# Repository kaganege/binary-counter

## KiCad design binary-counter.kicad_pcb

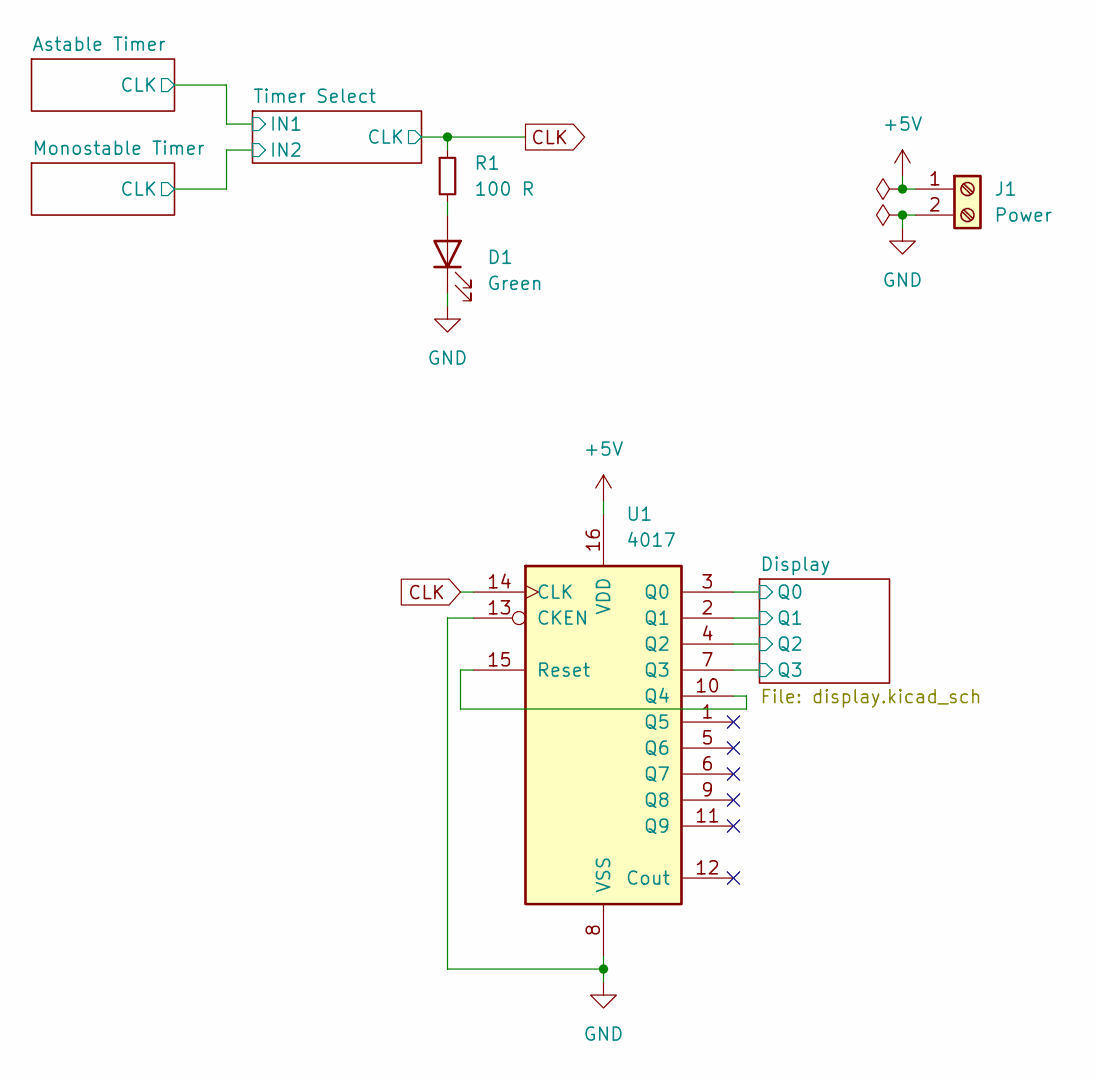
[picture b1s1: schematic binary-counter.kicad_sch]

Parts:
D1: Green; LED_D5.0mm
J1: Power; TerminalBlock_4Ucon_1x02_P3.50mm_Horizontal
R1: 100 R; R_Axial_DIN0207_L6.3mm_D2.5mm_P10.16mm_Horizontal
U1: 4017; DIP-16_W7.62mm_Socket

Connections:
+5V: J1.1, U1.16 (VDD); also elsewhere on the board
/Display/Q0: U1.3 (Q0); also elsewhere on the board
/Display/Q1: U1.2 (Q1); also elsewhere on the board
/Display/Q2: U1.4 (Q2); also elsewhere on the board
/Display/Q3: U1.7 (Q3); also elsewhere on the board
CLK: R1.1, U1.14 (CLK); also elsewhere on the board
GND: D1.1 (K), J1.2, U1.8 (VSS), U1.13 (CKEN); also elsewhere on the board
unnamed: D1.2 (A), R1.2
unnamed: U1.10 (Q4), U1.15 (Reset)

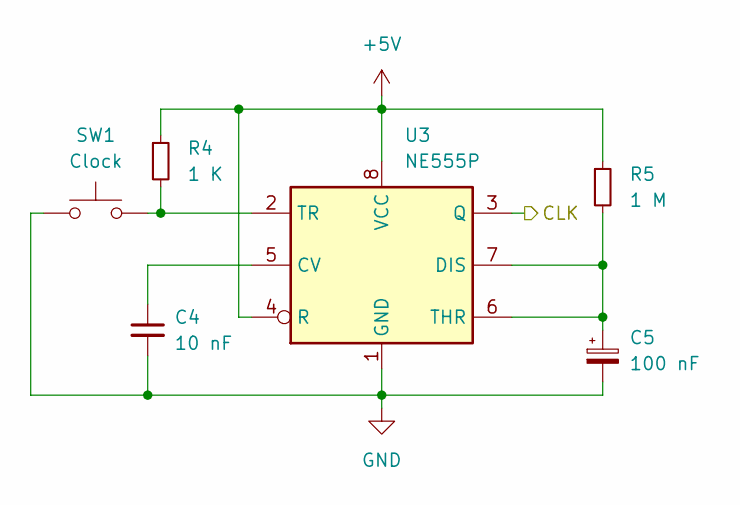
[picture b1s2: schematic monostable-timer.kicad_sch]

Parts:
C4: 10 nF; C_Disc_D7.5mm_W5.0mm_P5.00mm
C5: 100 nF; CP_Radial_D5.0mm_P2.50mm
R4: 1 K; R_Axial_DIN0207_L6.3mm_D2.5mm_P10.16mm_Horizontal
R5: 1 M; R_Axial_DIN0207_L6.3mm_D2.5mm_P10.16mm_Horizontal
SW1: Clock; SW_PUSH_6mm
U3: NE555P; DIP-8_W7.62mm_Socket

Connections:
+5V: R4.1, R5.1, U3.4 (R), U3.8 (VCC); also elsewhere on the board
/Monostable Timer/CLK: U3.3 (Q); also elsewhere on the board
GND: C4.2, C5.2, SW1.1, U3.1 (GND); also elsewhere on the board
unnamed: C4.1, U3.5 (CV)
unnamed: C5.1, R5.2, U3.6 (THR), U3.7 (DIS)
unnamed: R4.2, SW1.2, U3.2 (TR)

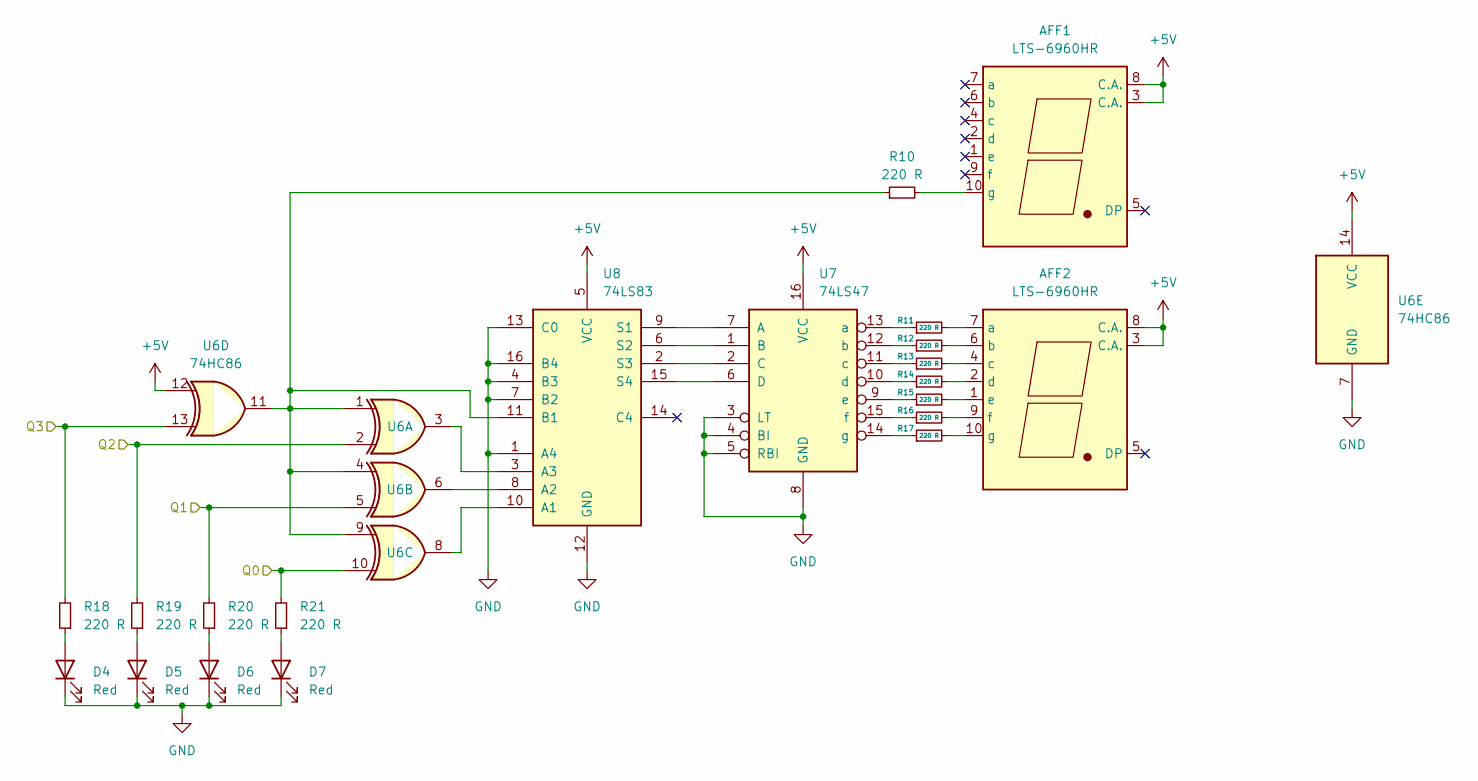
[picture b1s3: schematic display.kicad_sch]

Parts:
AFF1, AFF2: LTS-6960HR; 7SegmentLED_LTS6760_LTS6780
D4, D5, D6, D7: Red; LED_D5.0mm
R10, R11, R12, R13, R14, R15, R16, R17, R18, R19, R20, R21: 220 R; R_Axial_DIN0207_L6.3mm_D2.5mm_P10.16mm_Horizontal
U6: 74HC86; DIP-14_W7.62mm_Socket
U7: 74LS47; DIP-16_W7.62mm_Socket
U8: 74LS83; DIP-16_W7.62mm_Socket

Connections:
+5V: AFF1.3 (C.A.), AFF1.8 (C.A.), AFF2.3 (C.A.), AFF2.8 (C.A.), U6.12, U6.14 (VCC), U7.16 (VCC), U8.5 (VCC); also elsewhere on the board
/Display/Q0: R21.2, U6.10; also elsewhere on the board
/Display/Q1: R20.2, U6.5; also elsewhere on the board
/Display/Q2: R19.2, U6.2; also elsewhere on the board
/Display/Q3: R18.2, U6.13; also elsewhere on the board
GND: D4.1 (K), D5.1 (K), D6.1 (K), D7.1 (K), U6.7 (GND), U7.3 (LT), U7.4 (BI), U7.5 (RBI), U7.8 (GND), U8.1 (A4), U8.4 (B3), U8.7 (B2), U8.12 (GND), U8.13 (C0), U8.16 (B4); also elsewhere on the board
unnamed: AFF1.10 (g), R10.2
unnamed: AFF2.7 (a), R11.2
unnamed: AFF2.6 (b), R12.2
unnamed: AFF2.4 (c), R13.2
unnamed: AFF2.2 (d), R14.2
unnamed: AFF2.1 (e), R15.2
unnamed: AFF2.9 (f), R16.2
unnamed: AFF2.10 (g), R17.2
unnamed: D4.2 (A), R18.1
unnamed: D5.2 (A), R19.1
unnamed: D6.2 (A), R20.1
unnamed: D7.2 (A), R21.1
unnamed: U7.7 (A), U8.9 (S1)
unnamed: U7.1 (B), U8.6 (S2)
unnamed: U7.2 (C), U8.2 (S3)
unnamed: U7.6 (D), U8.15 (S4)
unnamed: R11.1, U7.13 (a)
unnamed: R12.1, U7.12 (b)
unnamed: R13.1, U7.11 (c)
unnamed: R14.1, U7.10 (d)
unnamed: R15.1, U7.9 (e)
unnamed: R16.1, U7.15 (f)
unnamed: R17.1, U7.14 (g)
unnamed: U6.8, U8.10 (A1)
unnamed: U6.6, U8.8 (A2)
unnamed: U6.3, U8.3 (A3)
unnamed: R10.1, U6.1, U6.4, U6.9, U6.11, U8.11 (B1)

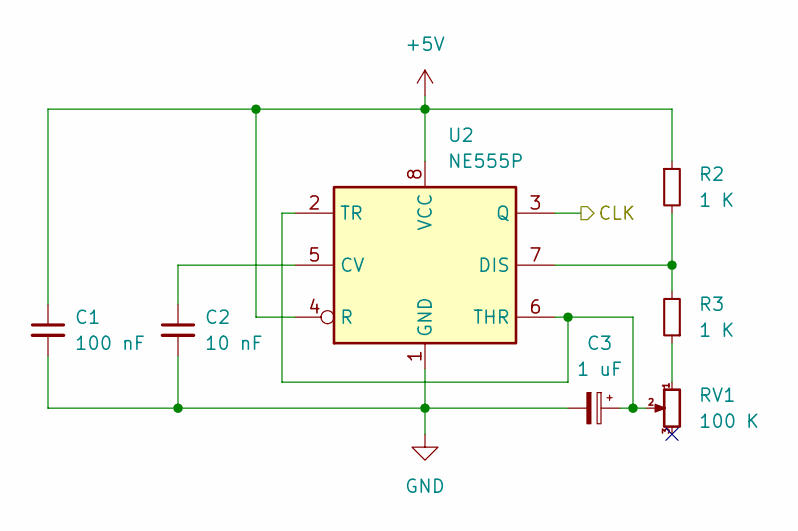
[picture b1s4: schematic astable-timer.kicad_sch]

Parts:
C1: 100 nF; C_Disc_D7.5mm_W5.0mm_P5.00mm
C2: 10 nF; C_Disc_D7.5mm_W5.0mm_P5.00mm
C3: 1 uF; CP_Radial_D5.0mm_P2.50mm
R2, R3: 1 K; R_Axial_DIN0207_L6.3mm_D2.5mm_P10.16mm_Horizontal
RV1: 100 K; Potentiometer_Bourns_3296W_Vertical
U2: NE555P; DIP-8_W7.62mm_Socket

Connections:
+5V: C1.1, R2.1, U2.4 (R), U2.8 (VCC); also elsewhere on the board
/Astable Timer/CLK: U2.3 (Q); also elsewhere on the board
GND: C1.2, C2.2, C3.2, U2.1 (GND); also elsewhere on the board
unnamed: R3.1, RV1.1
unnamed: C2.1, U2.5 (CV)
unnamed: R2.2, R3.2, U2.7 (DIS)
unnamed: C3.1, RV1.2, U2.2 (TR), U2.6 (THR)

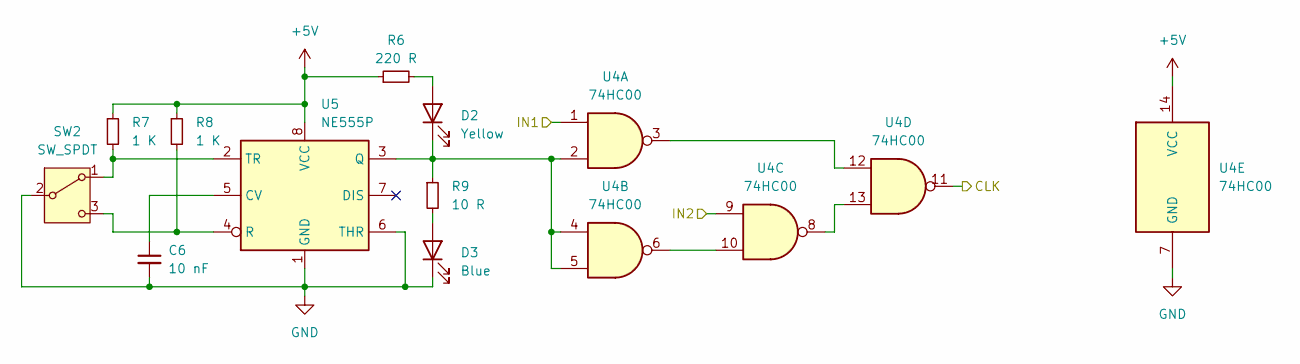
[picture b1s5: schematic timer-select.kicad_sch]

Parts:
C6: 10 nF; C_Disc_D7.5mm_W5.0mm_P5.00mm
D2: Yellow; LED_D5.0mm
D3: Blue; LED_D5.0mm
R6: 220 R; R_Axial_DIN0207_L6.3mm_D2.5mm_P10.16mm_Horizontal
R7, R8: 1 K; R_Axial_DIN0207_L6.3mm_D2.5mm_P10.16mm_Horizontal
R9: 10 R; R_Axial_DIN0207_L6.3mm_D2.5mm_P10.16mm_Horizontal
SW2: SW_SPDT; IC-205
U4: 74HC00; DIP-14_W7.62mm_Socket
U5: NE555P; DIP-8_W7.62mm_Socket

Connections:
+5V: R6.1, R7.1, R8.1, U4.14 (VCC), U5.8 (VCC); also elsewhere on the board
/Astable Timer/CLK: U4.1; also elsewhere on the board
/Monostable Timer/CLK: U4.9; also elsewhere on the board
CLK: U4.11; also elsewhere on the board
GND: C6.2, D3.1 (K), SW2.2 (B), U4.7 (GND), U5.1 (GND), U5.6 (THR); also elsewhere on the board
unnamed: D2.2 (A), R6.2
unnamed: D2.1 (K), R9.1, U4.2, U4.4, U4.5, U5.3 (Q)
unnamed: D3.2 (A), R9.2
unnamed: R7.2, SW2.1 (A), U5.2 (TR)
unnamed: R8.2, SW2.3 (C), U5.4 (R)
unnamed: U4.6, U4.10
unnamed: U4.3, U4.12
unnamed: U4.8, U4.13
unnamed: C6.1, U5.5 (CV)

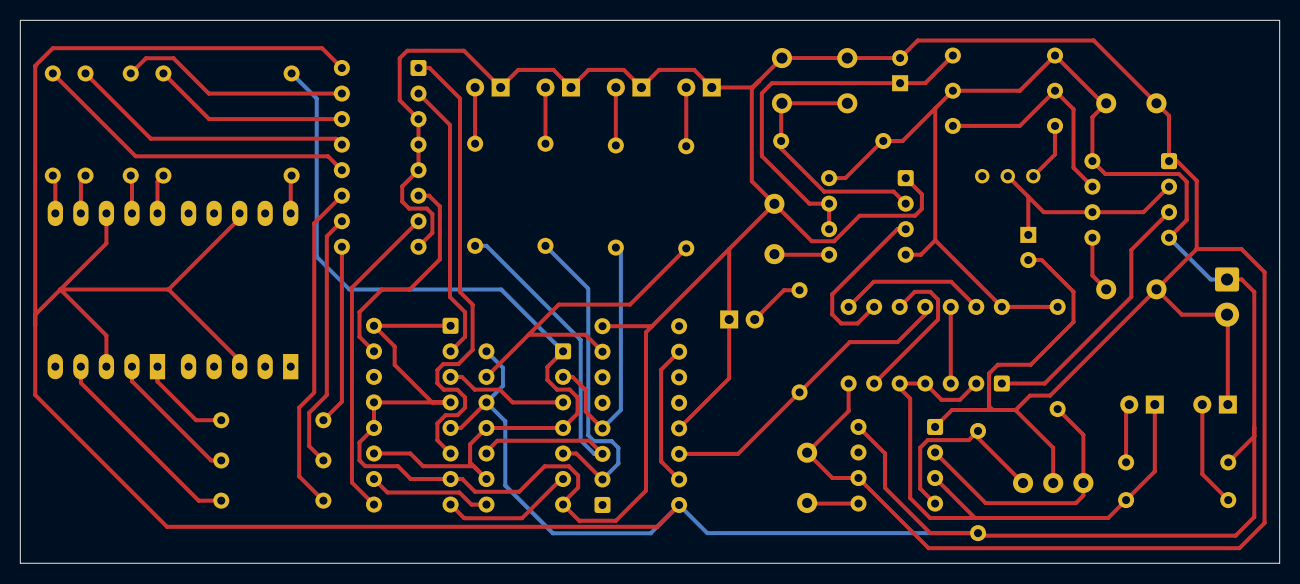
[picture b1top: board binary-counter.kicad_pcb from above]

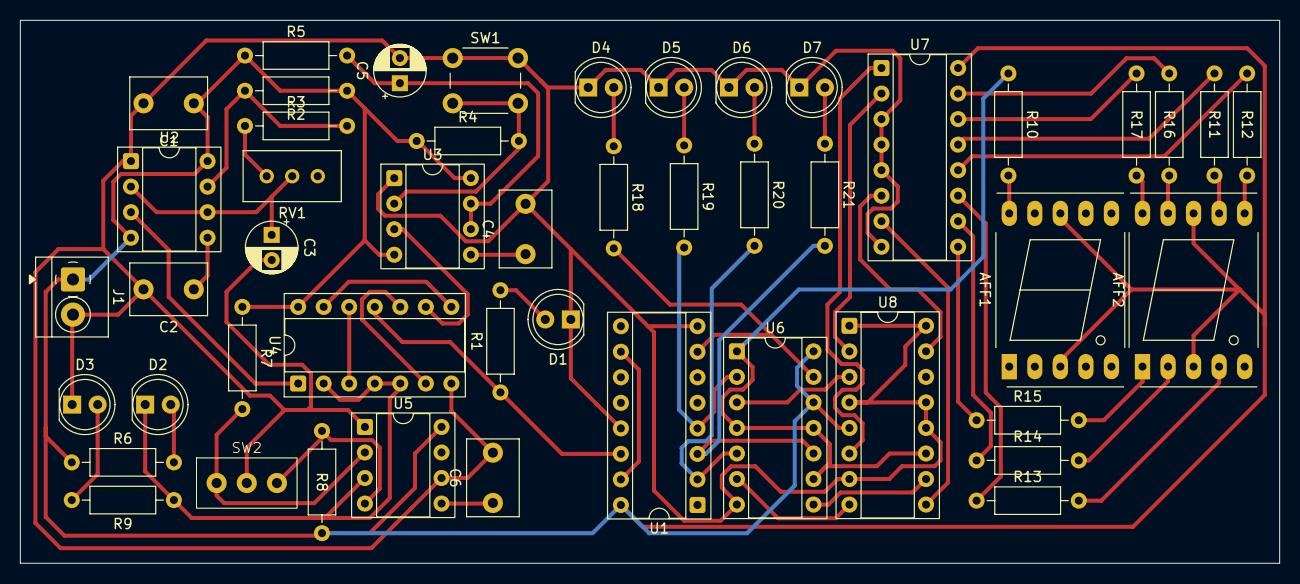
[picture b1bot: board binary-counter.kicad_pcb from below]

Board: 2 copper layers, 125.2 x 54.0 mm, 48 parts (48 on the bottom side), 54 nets.

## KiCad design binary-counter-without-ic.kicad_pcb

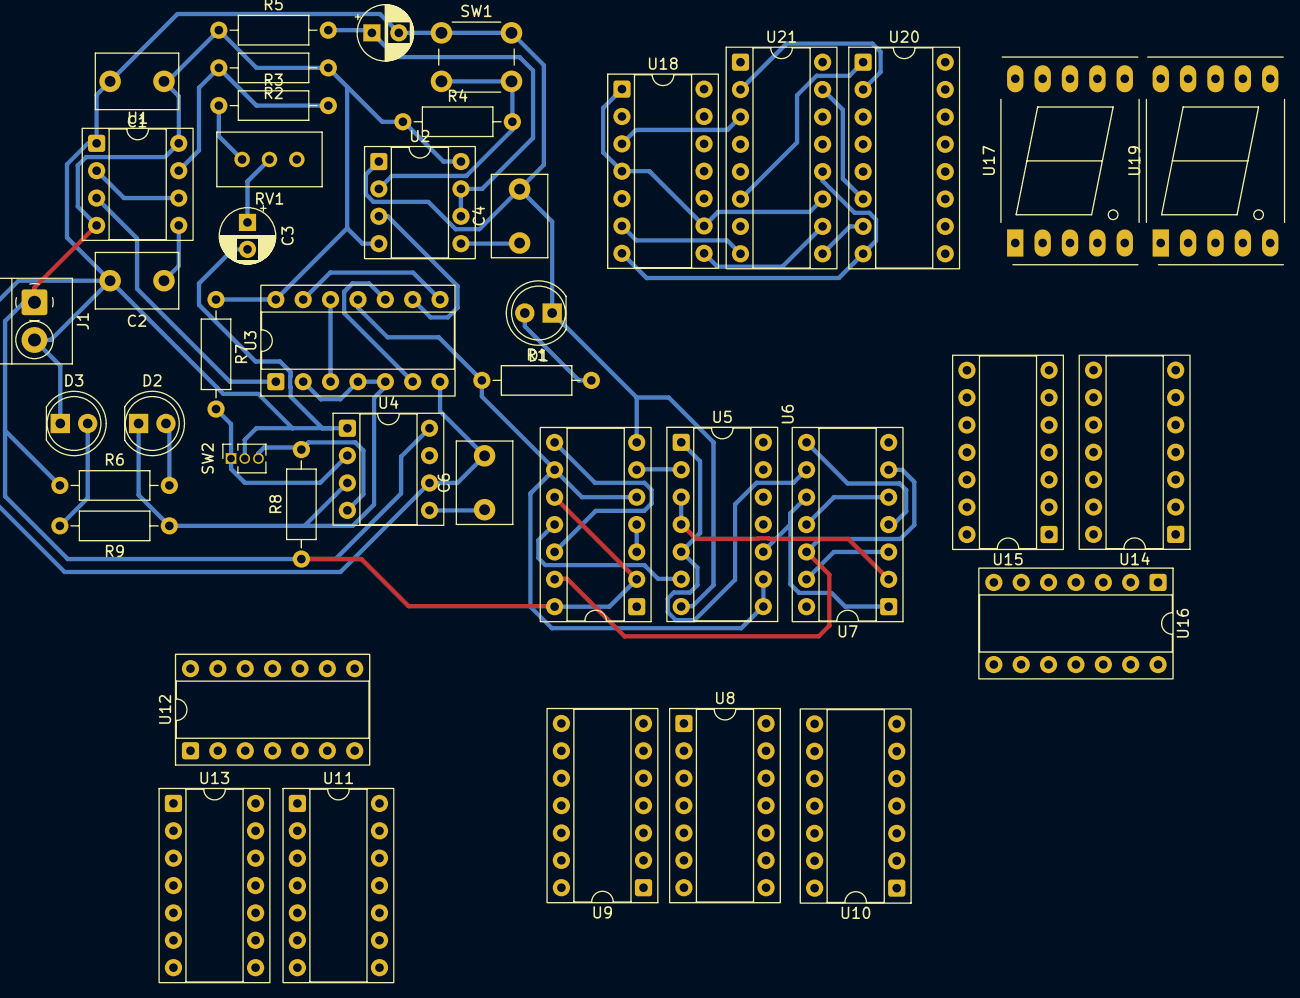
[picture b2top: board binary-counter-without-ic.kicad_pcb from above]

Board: 2 copper layers, 43 parts (0 on the bottom side), 81 nets.

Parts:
C1: 100 nF; C_Disc_D7.5mm_W5.0mm_P5.00mm
C2, C4, C6: 10 nF; C_Disc_D7.5mm_W5.0mm_P5.00mm
C3: 1 uF; CP_Radial_D5.0mm_P2.50mm
C5: 100 nF; CP_Radial_D5.0mm_P2.50mm
D1: Green; LED_D5.0mm
D2: Yellow; LED_D5.0mm
D3: Blue; LED_D5.0mm
J1: Power; TerminalBlock_4Ucon_1x02_P3.50mm_Horizontal
R1: 100 R; R_Axial_DIN0207_L6.3mm_D2.5mm_P10.16mm_Horizontal
R2, R3, R4, R7, R8: 1 K; R_Axial_DIN0207_L6.3mm_D2.5mm_P10.16mm_Horizontal
R5: 1 M; R_Axial_DIN0207_L6.3mm_D2.5mm_P10.16mm_Horizontal
R6: 220 R; R_Axial_DIN0207_L6.3mm_D2.5mm_P10.16mm_Horizontal
R9: 10 R; R_Axial_DIN0207_L6.3mm_D2.5mm_P10.16mm_Horizontal
RV1: 100 K; Potentiometer_Bourns_3296W_Vertical
SW1: Clock; SW_PUSH_6mm
SW2: SW_SPDT; PinSocket_1x03_P1.27mm_Vertical
U1, U2, U4: NE555P; DIP-8_W7.62mm_Socket
U3, U7, U10, U13, U16: 74HC00; DIP-14_W7.62mm_Socket
U5, U8, U11, U14: 74HC02; DIP-14_W7.62mm_Socket
U6, U9, U12, U15: 74HC08; DIP-14_W7.62mm_Socket
U17, U19: SM410561K; 7SegmentLED_LTS6760_LTS6780
U18: 74HC86; DIP-14_W7.62mm_Socket
U20: 74LS248; DIP-16_W7.62mm_Socket
U21: 74LS83; DIP-16_W7.62mm_Socket

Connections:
+5V: C1.1, J1.1, R2.1, R4.1, R5.1, R6.1, R7.1, R8.1, U1.4 (R), U1.8 (VCC), U2.4 (R), U2.8 (VCC), U3.14 (VCC), U4.8 (VCC), U5.14 (VCC), U6.2, U6.10, U6.14 (VCC), U7.14 (VCC), U8.14 (VCC), U9.2, U9.10, U9.14 (VCC), U10.14 (VCC), U11.14 (VCC), U12.2, U12.10, U12.14 (VCC), U13.14 (VCC), U14.14 (VCC), U15.2, U15.10, U15.14 (VCC), U16.14 (VCC), U18.14 (VCC), U20.16 (VCC), U21.5 (VCC)
/Astable Timer/CLK: U1.3 (Q), U3.1
/Master-Slave J-K Flip Flop1/3 Input AND Gate/AOUT: U8.2, U9.6
/Master-Slave J-K Flip Flop1/3 Input AND Gate/BOUT: U8.6, U9.11
/Master-Slave J-K Flip Flop1/S-R Latch/EN: U8.10, U10.1, U10.10
/Master-Slave J-K Flip Flop1/S-R Latch/R: U8.3, U8.4, U10.2
/Master-Slave J-K Flip Flop1/S-R Latch/S: U8.1, U8.5, U10.9
/Master-Slave J-K Flip Flop1/~Q: U9.1, U10.5, U10.11
/Master-Slave J-K Flip Flop2/3 Input AND Gate/AOUT: U11.2, U12.6
/Master-Slave J-K Flip Flop2/3 Input AND Gate/BOUT: U11.6, U12.11
/Master-Slave J-K Flip Flop2/S-R Latch/EN: U11.10, U13.1, U13.10
/Master-Slave J-K Flip Flop2/S-R Latch/R: U11.3, U11.4, U13.2
/Master-Slave J-K Flip Flop2/S-R Latch/S: U11.1, U11.5, U13.9
/Master-Slave J-K Flip Flop2/~Q: U12.1, U13.5, U13.11
/Master-Slave J-K Flip Flop3/3 Input AND Gate/AOUT: U14.2, U15.6
/Master-Slave J-K Flip Flop3/3 Input AND Gate/BOUT: U14.6, U15.11
/Master-Slave J-K Flip Flop3/Q: U15.13, U16.6, U16.12
/Master-Slave J-K Flip Flop3/S-R Latch/EN: U14.10, U16.1, U16.10
/Master-Slave J-K Flip Flop3/S-R Latch/R: U14.3, U14.4, U16.2
/Master-Slave J-K Flip Flop3/S-R Latch/S: U14.1, U14.5, U16.9
/Master-Slave J-K Flip Flop/3 Input AND Gate/AOUT: U5.2, U6.6
/Master-Slave J-K Flip Flop/3 Input AND Gate/BOUT: U5.6, U6.11
/Master-Slave J-K Flip Flop/S-R Latch/EN: U5.10, U7.1, U7.10
/Master-Slave J-K Flip Flop/S-R Latch/R: U5.3, U5.4, U7.2
/Master-Slave J-K Flip Flop/S-R Latch/S: U5.1, U5.5, U7.9
/Master-Slave J-K Flip Flop/~Q: U6.1, U7.5, U7.11
/Monostable Timer/CLK: U2.3 (Q), U3.9
CLK: R1.1, U3.11, U5.8, U5.9, U6.5, U6.9
CLK/2: U6.13, U7.6, U7.12, U8.8, U8.9, U9.5, U9.9, U18.10
CLK/4: U9.13, U10.6, U10.12, U11.8, U11.9, U12.5, U12.9, U18.5
CLK/8: U12.13, U13.6, U13.12, U14.8, U14.9, U15.5, U15.9, U18.2
GND: C1.2, C2.2, C3.2, C4.2, C5.2, C6.2, D1.1 (K), D3.1 (K), J1.2, SW1.1, SW2.2 (B), U1.1 (GND), U2.1 (GND), U3.7 (GND), U4.1 (GND), U4.6 (THR), U5.7 (GND), U6.7 (GND), U7.7 (GND), U8.7 (GND), U9.7 (GND), U10.7 (GND), U11.7 (GND), U12.7 (GND), U13.7 (GND), U14.7 (GND), U15.7 (GND), U16.7 (GND), U17.3 (CC), U17.8 (CC), U18.7 (GND), U19.3 (CC), U19.8 (CC), U20.8 (GND), U21.12 (GND)
unnamed: C3.1, RV1.2
unnamed: D1.2 (A), R1.2
unnamed: D2.2 (A), R6.2
unnamed: D2.1 (K), R9.1, U3.2, U3.4, U3.5, U4.3 (Q)
unnamed: D3.2 (A), R9.2
unnamed: R3.1, RV1.1
unnamed: R7.2, SW2.1 (A), U4.2 (TR)
unnamed: R8.2, SW2.3 (C), U4.4 (R)
unnamed: C2.1, U1.5 (CV)
unnamed: R2.2, R3.2, U1.7 (DIS)
unnamed: U1.2 (TR), U1.6 (THR)
unnamed: C4.1, U2.5 (CV)
unnamed: C5.1, R5.2, U2.6 (THR), U2.7 (DIS)
unnamed: R4.2, SW1.2, U2.2 (TR)
unnamed: U3.6, U3.10
unnamed: U3.3, U3.12
unnamed: U3.8, U3.13
unnamed: C6.1, U4.5 (CV)
unnamed: U6.3, U6.4
unnamed: U6.8, U6.12
unnamed: U7.4, U7.8
unnamed: U7.3, U7.13
unnamed: U9.3, U9.4
unnamed: U9.8, U9.12
unnamed: U10.4, U10.8
unnamed: U10.3, U10.13
unnamed: U12.3, U12.4
unnamed: U12.8, U12.12
unnamed: U13.4, U13.8
unnamed: U13.3, U13.13
unnamed: U15.3, U15.4
unnamed: U15.8, U15.12
unnamed: U16.4, U16.8
unnamed: U16.3, U16.13
unnamed: U19.7 (A), U20.13 (a)
unnamed: U19.6 (B), U20.12 (b)
unnamed: U19.4 (C), U20.11 (c)
unnamed: U19.2 (D), U20.10 (d)
unnamed: U19.1 (E), U20.9 (e)
unnamed: U19.9 (F), U20.15 (f)
unnamed: U19.10 (G), U20.14 (g)
unnamed: U20.7 (A), U21.9 (S1)
unnamed: U20.1 (B), U21.6 (S2)
unnamed: U20.2 (C), U21.2 (S3)
unnamed: U20.6 (D), U21.15 (S4)
unnamed: U18.8, U21.10 (A1)
unnamed: U18.6, U21.8 (A2)
unnamed: U18.3, U21.3 (A3)
~CLK/16: U15.1, U16.5, U16.11, U17.10 (G), U18.1, U18.4, U18.9, U21.11 (B1)

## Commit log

2025-04-29 finished
2025-05-01 the end
